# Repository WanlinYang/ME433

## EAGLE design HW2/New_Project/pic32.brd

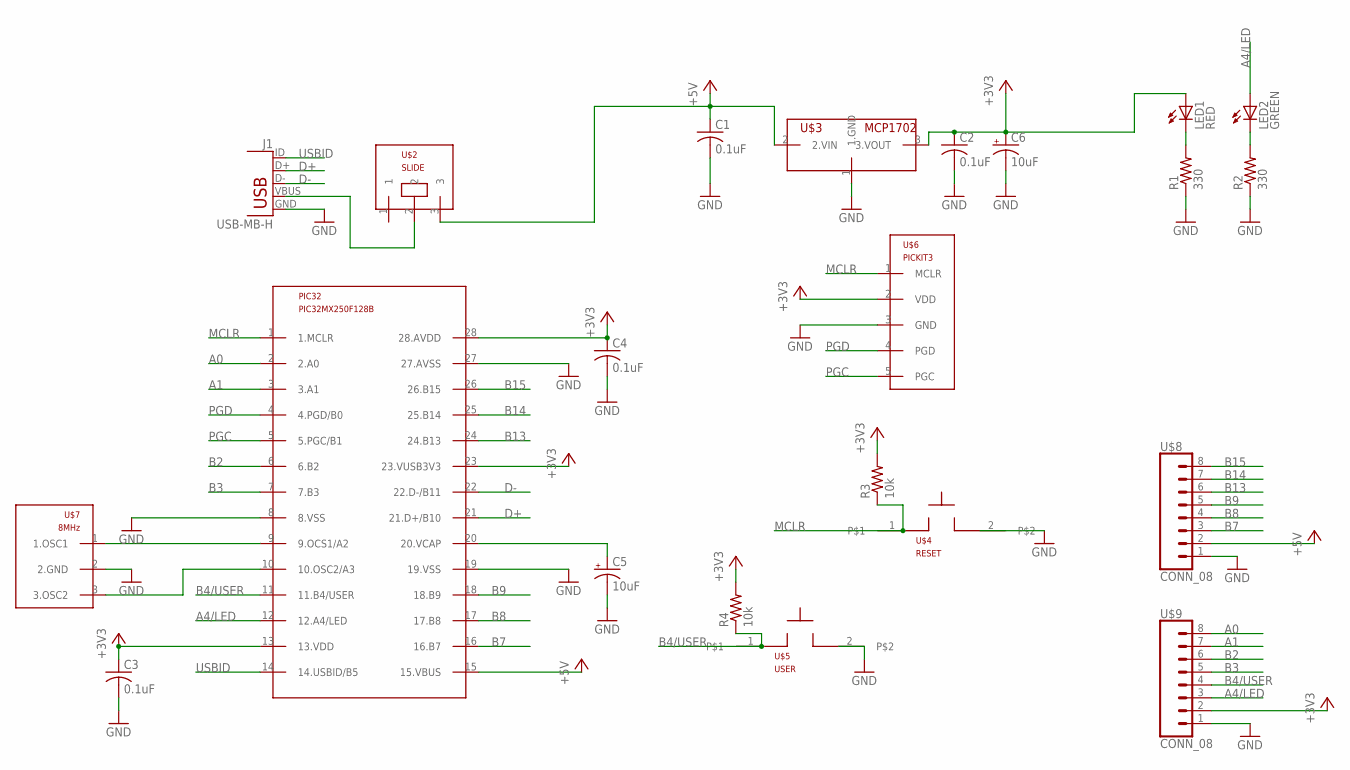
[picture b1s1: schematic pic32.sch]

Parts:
C1, C2, C3, C4: 0.1uF; C025-025X050
C5, C6: 10uF; B45181B
J1: USB-MB-H
LED1: RED; LED3MM
LED2: GREEN; LED3MM
PIC32: PIC32MX250F128B; DIL28-3
R1, R2: 330; 0207/10
R3, R4: 10k; 0207/10
U$2: SLIDE
U$3: MCP1702; TO92
U$4: RESET; PB
U$5: USER; PB
U$6: PICKIT3; 1X05
U$7: 8MHz; OSC
U$8, U$9: CONN_08; 1X08

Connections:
+3V3: C2.1, C3.1, C4.1, C6.+, LED1.A, PIC32.13 (13.VDD), PIC32.23 (23.VUSB3V3), PIC32.28 (28.AVDD), R3.2, R4.2, U$3.3 (3.VOUT), U$6.2 (VDD), U$9.2
+5V: C1.1, PIC32.15 (15.VBUS), U$2.3, U$3.2 (2.VIN), U$8.2
A0: PIC32.2 (2.A0), U$9.8
A1: PIC32.3 (3.A1), U$9.7
A4/LED: LED2.A, PIC32.12 (12.A4/LED), U$9.3
B2: PIC32.6 (6.B2), U$9.6
B3: PIC32.7 (7.B3), U$9.5
B4/USER: PIC32.11 (11.B4/USER), R4.1, U$5.1, U$9.4
B7: PIC32.16 (16.B7), U$8.3
B8: PIC32.17 (17.B8), U$8.4
B9: PIC32.18 (18.B9), U$8.5
B13: PIC32.24 (24.B13), U$8.6
B14: PIC32.25 (25.B14), U$8.7
B15: PIC32.26 (26.B15), U$8.8
D+: J1.D+, PIC32.21 (21.D+/B10)
D-: J1.D-, PIC32.22 (22.D-/B11)
GND: C1.2, C2.2, C3.2, C4.2, C5.-, C6.-, J1.GND, PIC32.8 (8.VSS), PIC32.19 (19.VSS), PIC32.27 (27.AVSS), R1.1, R2.1, U$3.1 (1.GND), U$4.2, U$5.2, U$6.3 (GND), U$7.2 (2.GND), U$8.1, U$9.1
MCLR: PIC32.1 (1.MCLR), R3.1, U$4.1, U$6.1 (MCLR)
unnamed: J1.VBUS, U$2.2
unnamed: PIC32.10 (10.OSC2/A3), U$7.3 (3.OSC2)
unnamed: LED1.K (C), R1.2
unnamed: LED2.K (C), R2.2
unnamed: PIC32.9 (9.OCS1/A2), U$7.1 (1.OSC1)
unnamed: C5.+, PIC32.20 (20.VCAP)
PGC: PIC32.5 (5.PGC/B1), U$6.5 (PGC)
PGD: PIC32.4 (4.PGD/B0), U$6.4 (PGD)
USBID: J1.ID, PIC32.14 (14.USBID/B5)

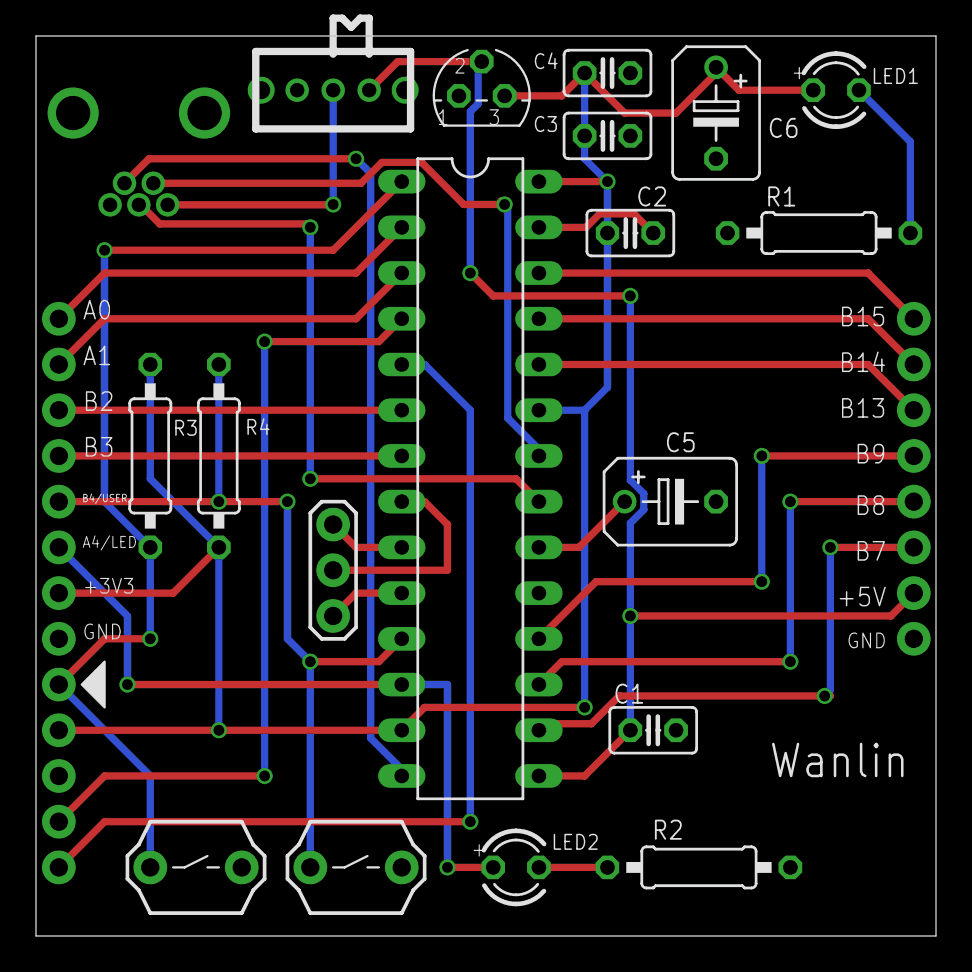
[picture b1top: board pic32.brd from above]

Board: 2 copper layers, 50.0 x 50.0 mm, 22 parts (0 on the bottom side), 27 nets.

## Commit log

2017-03-29 :octocat: Added .gitattributes & .gitignore files
2017-03-29 me433
2017-03-29 delete
2017-03-29 5:51
2017-03-29 6.44
2017-03-30 9.08
2017-03-30 pictures9.32
2017-03-30 pictures9.33
2017-04-01 eagle
2017-04-04 library
2017-04-07 gerber
2017-04-11 plot
2017-04-11 pictures
2017-04-14 diagram
2017-04-26 Harmony
2017-05-04 LED Flash
2017-05-05 mouse
2017-05-12 Android
2017-05-12 camera
2017-05-25 Android USB
2017-05-25 CAD Designs
2017-06-04 motor
2017-06-04 image
2017-06-05 Navigator
